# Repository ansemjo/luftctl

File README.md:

# luftctl

Small ESP32-C3 controller board to power two 12V PWM fans from a single USB plug.

## hardware

Schematic and PCB design can be found in [`hardware/`](hardware/). It is a KiCAD 6 project.

The schematic is available as [a PDF](schematic.pdf).

## firmware

The first simple test just loops through {`5V/off`, `5V/on`, `12V/off`, `12V/on`} with every button press.

Download MicroPython from [micropython.org/download/esp32c3-usb/](https://micropython.org/download/esp32c3-usb/) and flash it with:

```
esptool.py --chip esp32c3 --port /dev/ttyACM0 erase_flash
esptool.py --chip esp32c3 --port /dev/ttyACM0 --baud 460800 write_flash -z 0x0 esp32c3-*.bin
```

Then install a virtualenv with `adafruit-ampy` and upload the [`main.py`](main.py):

```
ampy -p /dev/ttyACM0 put main.py
ampy -p /dev/ttyACM0 reset --hard
```

The red LED will blink upon every state change.

## images

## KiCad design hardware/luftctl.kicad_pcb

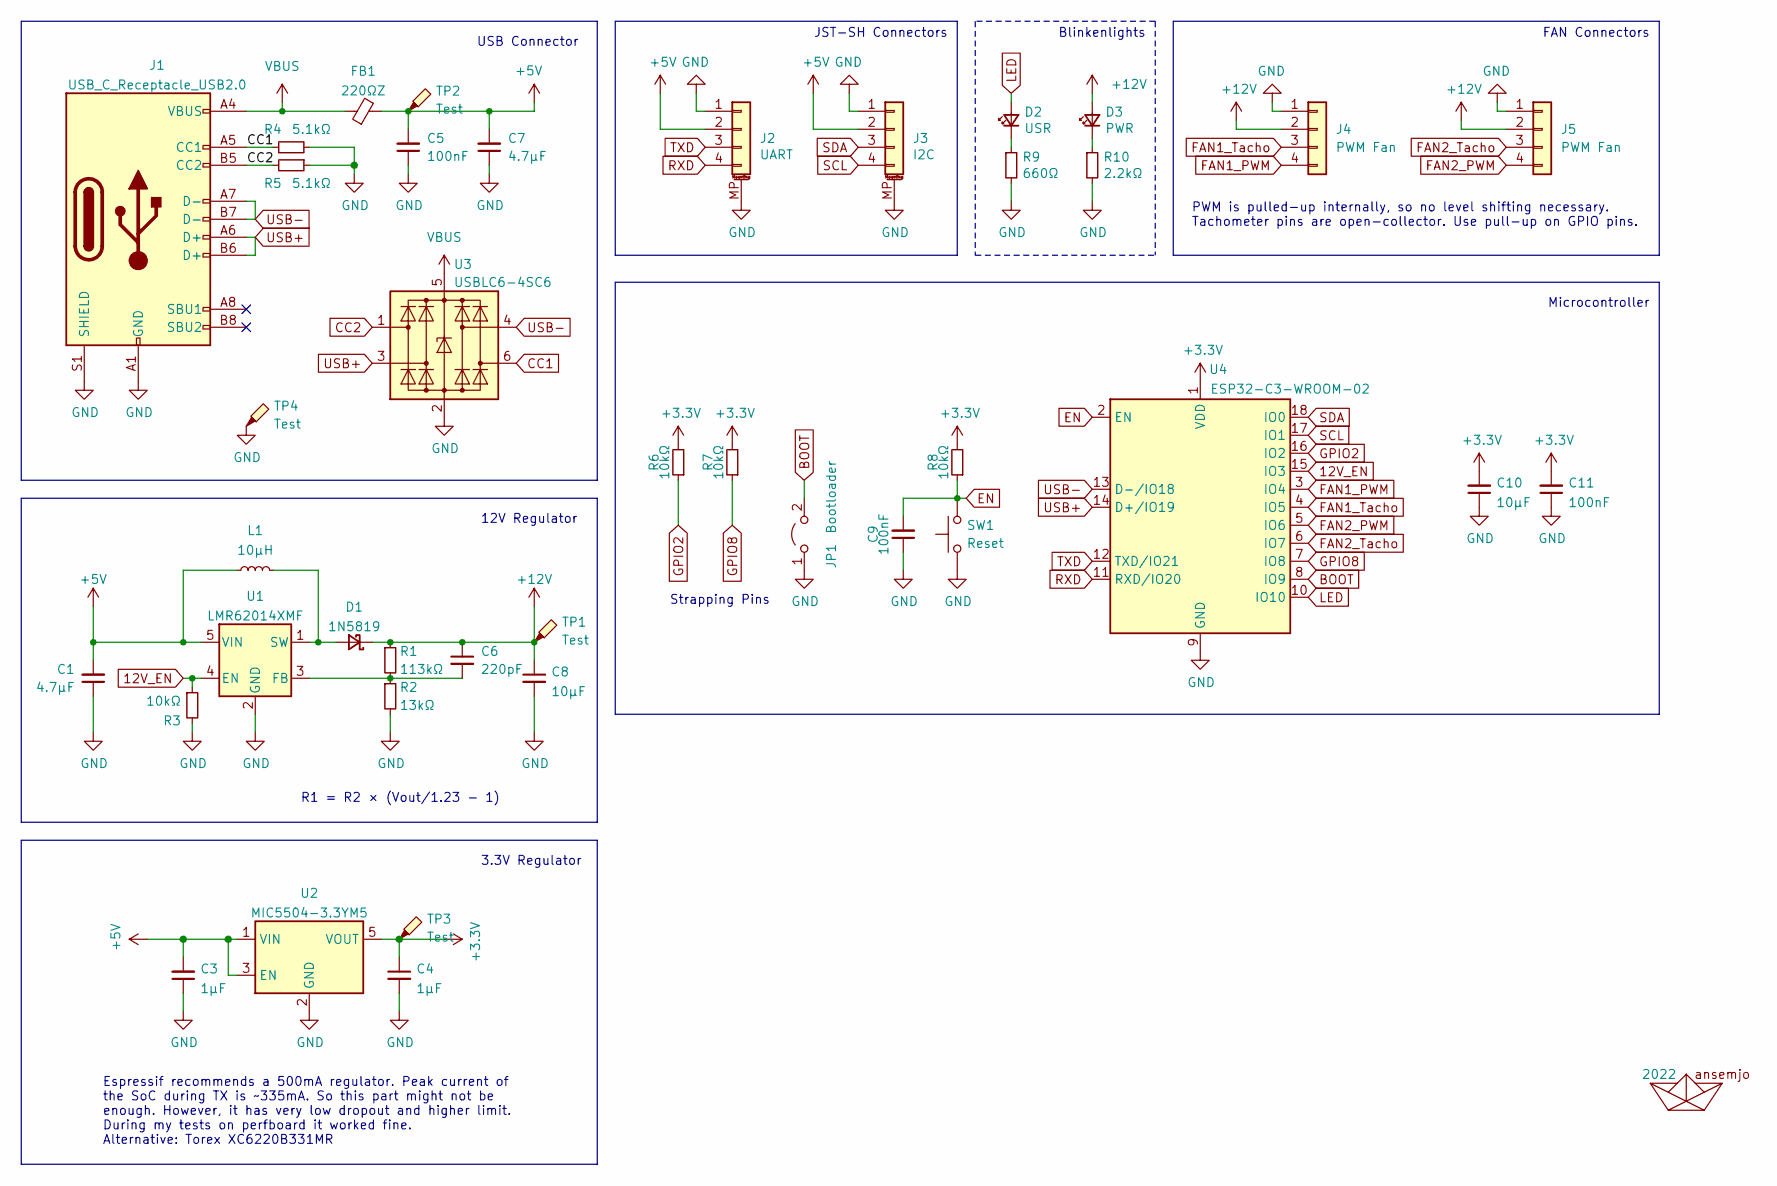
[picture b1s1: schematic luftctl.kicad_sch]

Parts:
A1: 2022; ahoi
C1, C7: 4.7µF; C_0805_2012Metric_Pad1.18x1.45mm_HandSolder
C3, C4: 1µF; C_0805_2012Metric_Pad1.18x1.45mm_HandSolder
C5, C9, C11: 100nF; C_0805_2012Metric_Pad1.18x1.45mm_HandSolder
C6: 220pF; C_0805_2012Metric_Pad1.18x1.45mm_HandSolder
C8, C10: 10µF; C_0805_2012Metric_Pad1.18x1.45mm_HandSolder
D1: 1N5819; D_SOD-123
D2: USR; LED_0805_2012Metric_Pad1.15x1.40mm_HandSolder
D3: PWR; LED_0805_2012Metric_Pad1.15x1.40mm_HandSolder
FB1: 220ΩZ; L_0805_2012Metric_Pad1.15x1.40mm_HandSolder
J1: USB_C_Receptacle_USB2.0; USB_C_Receptacle_HRO_TYPE-C-31-M-12
J2: UART; JST_SH_SM04B-SRSS-TB_1x04-1MP_P1.00mm_Horizontal
J3: I2C; JST_SH_SM04B-SRSS-TB_1x04-1MP_P1.00mm_Horizontal
J4, J5: PWM Fan; FanPinHeader_1x04_P2.54mm_Vertical
JP1: Bootloader; SW_SPST_PTS810
L1: 10µH; L_Bourns_SRN6045TA
R1: 113kΩ; R_0805_2012Metric_Pad1.20x1.40mm_HandSolder
R2: 13kΩ; R_0805_2012Metric_Pad1.20x1.40mm_HandSolder
R3, R6, R7, R8: 10kΩ; R_0805_2012Metric_Pad1.20x1.40mm_HandSolder
R4, R5: 5.1kΩ; R_0805_2012Metric_Pad1.20x1.40mm_HandSolder
R9: 660Ω; R_0805_2012Metric_Pad1.20x1.40mm_HandSolder
R10: 2.2kΩ; R_0805_2012Metric_Pad1.20x1.40mm_HandSolder
SW1: Reset; SW_SPST_PTS810
TP1, TP2, TP3, TP4: Test; TestPoint_THTPad_D1.5mm_Drill0.7mm
U1: LMR62014XMF; SOT-23-5
U2: MIC5504-3.3YM5; SOT-23-5
U3: USBLC6-4SC6; SOT-23-6; MPN USBLC6-4SC6; Digi-Key_PN 497-4492-1-ND
U4: ESP32-C3-WROOM-02; ESP-WROOM-02

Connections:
12V_EN: R3.1, U1.4 (EN), U4.15 (IO3)
+3V3: C4.1, C10.2, C11.2, R6.2, R7.2, R8.2, TP3.1, U2.5 (VOUT), U4.1 (VDD)
+5V: C1.2, C3.2, C5.2, C7.2, FB1.2, J2.2, J3.2, L1.1, TP2.1, U1.5 (VIN), U2.1 (VIN), U2.3 (EN)
+12V: C6.1, C8.1, D1.1 (K), D3.2 (A), J4.2, J5.2, R1.1, TP1.1
BOOT: JP1.2 (B), U4.8 (IO9)
CC1: J1.A5 (CC1), R4.1, U3.6 (I/O4)
CC2: J1.B5 (CC2), R5.2, U3.1 (I/O1)
EN: C9.2, R8.1, SW1.2, U4.2 (EN)
FAN1_PWM: J4.4, U4.3 (IO4)
FAN1_Tacho: J4.3, U4.4 (IO5)
FAN2_PWM: J5.4, U4.5 (IO6)
FAN2_Tacho: J5.3, U4.6 (IO7)
GND: C1.1, C3.1, C4.2, C5.1, C7.1, C8.2, C9.1, C10.1, C11.1, J1.A1 (GND), J1.A12 (GND), J1.B1 (GND), J1.B12 (GND), J1.S1 (SHIELD), J2.1, J2.MP (MountPin), J3.1, J3.MP (MountPin), J4.1, J5.1, JP1.1 (A), R2.2, R3.2, R4.2, R5.1, R9.2, R10.2, SW1.1, TP4.1, U1.2 (GND), U2.2 (GND), U3.2 (GND), U4.9 (GND), U4.19 (GND)
GPIO2: R6.1, U4.16 (IO2)
GPIO8: R7.1, U4.7 (IO8)
LED: D2.2 (A), U4.10 (IO10)
unnamed: C6.2, R1.2, R2.1, U1.3 (FB)
unnamed: D1.2 (A), L1.2, U1.1 (SW)
unnamed: D2.1 (K), R9.1
unnamed: D3.1 (K), R10.1
RXD: J2.4, U4.11 (RXD/IO20)
SCL: J3.4, U4.17 (IO1)
SDA: J3.3, U4.18 (IO0)
TXD: J2.3, U4.12 (TXD/IO21)
USB+: J1.A6 (D+), J1.B6 (D+), U3.3 (I/O2), U4.14 (D+/IO19)
USB-: J1.A7 (D-), J1.B7 (D-), U3.4 (I/O3), U4.13 (D-/IO18)
VBUS: FB1.1, J1.A4 (VBUS), J1.A9 (VBUS), J1.B4 (VBUS), J1.B9 (VBUS), U3.5 (VBUS)

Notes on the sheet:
3.3V Regulator
PWM is pulled-up internally, so no level shifting necessary. Tachometer pins are open-collector. Use pull-up on GPIO pins.
12V Regulator
Strapping Pins
USB Connector
JST-SH Connectors
Microcontroller
FAN Connectors
R1 = R2 × (Vout/1.23 - 1)
Blinkenlights
Espressif recommends a 500mA regulator. Peak current of the SoC during TX is ~335mA. So this part might not be enough. However, it has very low dropout and higher limit. During my tests on perfboard it worked fine. Alternative: Torex XC6220B331MR

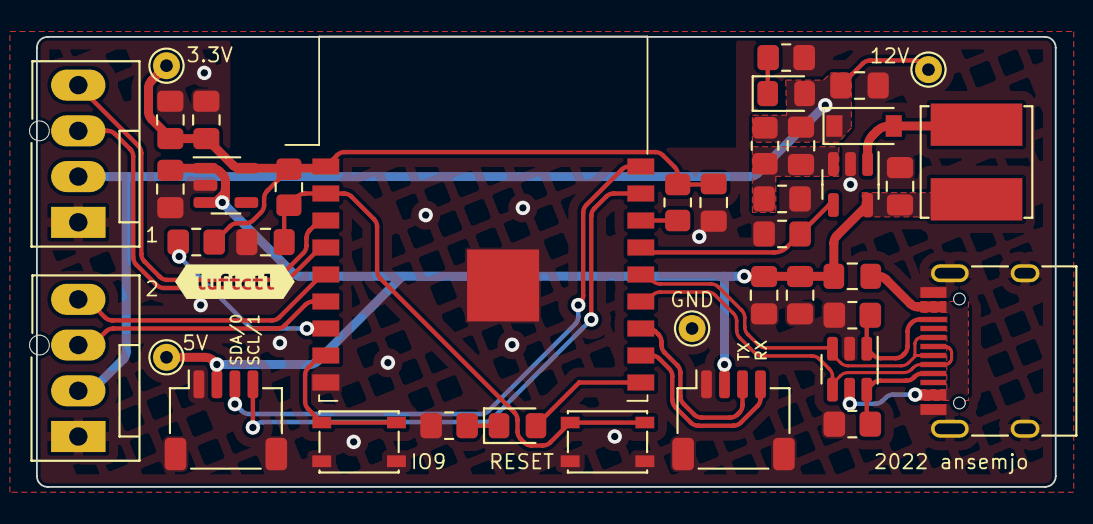
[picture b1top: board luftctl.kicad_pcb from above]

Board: 2 copper layers, 56.6 x 25.0 mm, 41 parts (0 on the bottom side), 27 nets.

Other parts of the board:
kibuzzard-61E47F36: G***; kibuzzard-61E47F36

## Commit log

2021-09-02 start project by copying my previous rackluefter schematic
2022-01-16 redesigned schematic for esp32-c3 module, dummy pcb
2022-01-16 finished pcb layout
2022-01-16 update readme with new renders and schematic
2022-01-16 add kikit panelization config
2022-01-16 add gerbers sent to jlcpcb for fab
2022-01-16 add ibom for soldering later
2022-01-26 update with sample µpy code and photo
2022-01-26 add schematic link in readme
2022-01-27 update sample code to handle button presses
2022-01-27 oops, off by one
2022-01-27 one more photo of assembly with two fans
2022-02-01 improve main.py with pwm for fans and led
